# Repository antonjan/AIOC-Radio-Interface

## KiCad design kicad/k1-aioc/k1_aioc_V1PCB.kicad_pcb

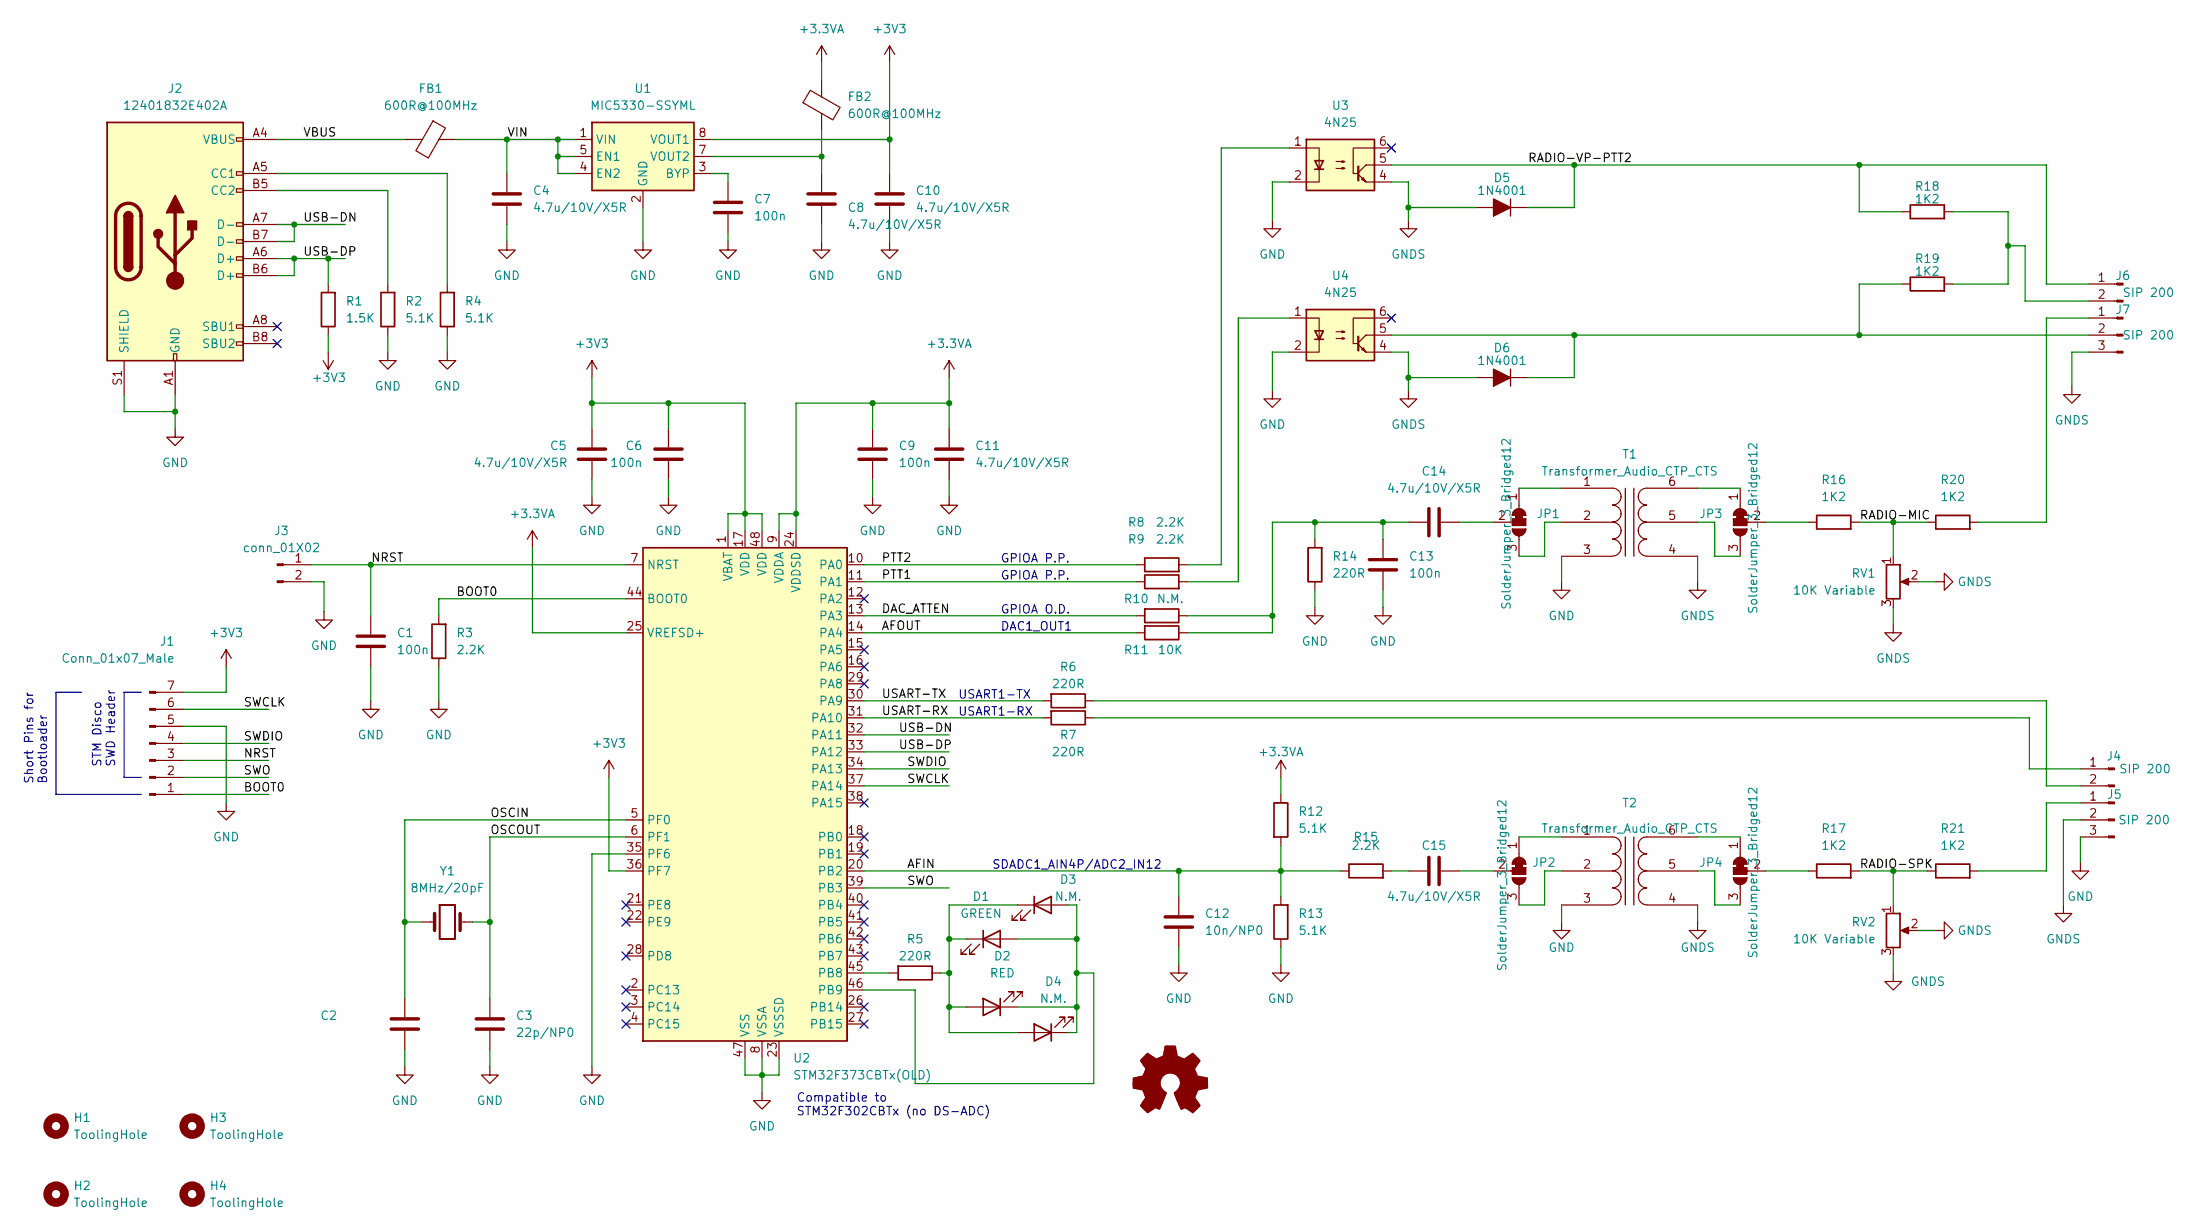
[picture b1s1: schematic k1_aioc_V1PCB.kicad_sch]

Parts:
C1, C6, C7, C9, C13: 100n; C_0805_2012Metric_Pad1.18x1.45mm_HandSolder; LCSC C14663
C2: LCSC C1653
C3: 22p/NP0; C_0805_2012Metric_Pad1.18x1.45mm_HandSolder; LCSC C1653
C4, C5, C8, C10, C11, C14, C15: 4.7u/10V/X5R; C_0805_2012Metric_Pad1.18x1.45mm_HandSolder; LCSC C19666
C12: 10n/NP0; C_0805_2012Metric_Pad1.18x1.45mm_HandSolder; LCSC C57112
D1: GREEN; LED_0805_2012Metric_Pad1.15x1.40mm_HandSolder; LCSC C72043
D2: RED; LED_0805_2012Metric_Pad1.15x1.40mm_HandSolder; LCSC C2286
D3, D4: N.M.; LED_0805_2012Metric_Pad1.15x1.40mm_HandSolder
D5, D6: 1N4001; D_0805_2012Metric_Pad1.15x1.40mm_HandSolder
FB1, FB2: 600R@100MHz; L_0805_2012Metric_Pad1.15x1.40mm_HandSolder; LCSC C1002
H1, H2, H3, H4: ToolingHole; MountingHole_3.2mm_M3_DIN965_Pad_TopBottom
J1: Conn_01x07_Male; PinHeader_1x07_P1.27mm_Vertical
J2: 12401832E402A; USB_C_Receptacle_Amphenol_12401832E40-2A; LCSC C464604
J3: conn_01X02; PinHeader_1x02_P2.54mm_Vertical
J4, J6: SIP 200; TerminalBlock_bornier-2_P5.08mm
J5, J7: SIP 200; TerminalBlock_bornier-3_P5.08mm
JP1, JP2, JP3, JP4: SolderJumper_3_Bridged12; SolderJumper-3_P1.3mm_Bridged12_RoundedPad1.0x1.5mm_NumberL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
R1: 1.5K; R_0805_2012Metric_Pad1.20x1.40mm_HandSolder; LCSC C22843
R2, R4, R12, R13: 5.1K; R_0805_2012Metric_Pad1.20x1.40mm_HandSolder; LCSC C23186
R3, R8, R9, R15: 2.2K; R_0805_2012Metric_Pad1.20x1.40mm_HandSolder; LCSC C4190
R5, R6, R7, R14: 220R; R_0805_2012Metric_Pad1.20x1.40mm_HandSolder; LCSC C22962
R10: N.M.; R_0805_2012Metric_Pad1.20x1.40mm_HandSolder
R11: 10K; R_0805_2012Metric_Pad1.20x1.40mm_HandSolder; LCSC C25804
R16, R17, R18, R19, R20, R21: 1K2; R_0805_2012Metric_Pad1.20x1.40mm_HandSolder
RV1, RV2: 10K Variable; Potentiometer_Bourns_3314G_Vertical
T1, T2: Transformer_Audio_CTP_CTS; Transformer_Bourns_SM-LP-5001
U1: MIC5330-SSYML; Micrel_MLF-8-1EP_2x2mm_P0.5mm_EP0.6x1.2mm; LCSC C144168
U2: STM32F373CBTx(OLD); LQFP-48_7x7mm_P0.5mm; LCSC C94046
U3, U4: 4N25; DIP-6_W8.89mm_SMDSocket_LongPads
Y1: 8MHz/20pF; Crystal_8MHz_SMD_11.40mm; LCSC C115962

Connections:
+3.3VA: C9.1, C11.1, FB2.1, R12.1, U2.9 (VDDA), U2.24 (VDDSD), U2.25 (VREFSD+)
+3V3: C5.1, C6.1, C10.1, J1.7, R1.1, U1.8 (VOUT1), U2.1 (VBAT), U2.17 (VDD), U2.36 (PF7), U2.48 (VDD)
/AFIN: C12.1, R12.2, R13.2, R15.1, U2.20 (PB2)
/AFOUT: R11.2, U2.14 (PA4)
/BOOT0: J1.1, R3.2, U2.44 (BOOT0)
/DAC_ATTEN: R10.2, U2.13 (PA3)
/NRST: C1.1, J1.3, J3.1, U2.7 (NRST)
/OSCIN: C2.1, U2.5 (PF0), Y1.1
/OSCOUT: C3.1, U2.6 (PF1), Y1.2
/PTT1: R9.1, U2.11 (PA1)
/PTT2: R8.1, U2.10 (PA0)
/RADIO-MIC: R16.2, R20.1, RV1.1
/RADIO-SPK: R17.2, R21.1, RV2.1
/RADIO-VP-PTT2: D5.1 (K), J6.1, R18.1, U3.5
/SWCLK: J1.6, U2.37 (PA14)
/SWDIO: J1.4, U2.34 (PA13)
/SWO: J1.2, U2.39 (PB3)
/USART-RX: R7.2, U2.31 (PA10)
/USART-TX: R6.2, U2.30 (PA9)
/USB-DN: J2.A7 (D-), J2.B7 (D-), U2.32 (PA11)
/USB-DP: J2.A6 (D+), J2.B6 (D+), R1.2, U2.33 (PA12)
/VBUS: FB1.2, J2.A4 (VBUS), J2.A9 (VBUS), J2.B4 (VBUS), J2.B9 (VBUS)
/VIN: C4.1, FB1.1, U1.1 (VIN), U1.4 (EN2), U1.5 (EN1)
GND: C1.2, C2.2, C3.2, C4.2, C5.2, C6.2, C7.2, C8.2, C9.2, C10.2, C11.2, C12.2, C13.2, J1.5, J2.A1 (GND), J2.A12 (GND), J2.B1 (GND), J2.B12 (GND), J2.S1 (SHIELD), J3.2, J5.3, R2.1, R3.1, R4.1, R13.1, R14.1, T1.3 (PR2), T2.3 (PR2), U1.2 (GND), U1.9 (GND), U2.8 (VSSA), U2.23 (VSSSD), U2.35 (PF6), U2.47 (VSS), U3.2, U4.2
GNDS: D5.2 (A), D6.2 (A), J5.2, J7.3, RV1.2, RV1.3, RV2.2, RV2.3, T1.4 (S1), T2.4 (S1), U3.4, U4.4
unnamed: C7.1, U1.3 (BYP)
unnamed: C8.1, FB2.2, U1.7 (VOUT2)
unnamed: C13.1, C14.1, R10.1, R11.1, R14.2
unnamed: C14.2, JP1.2 (C)
unnamed: C15.1, R15.2
unnamed: C15.2, JP2.2 (C)
unnamed: D1.1 (K), D2.2 (A), D3.1 (K), D4.2 (A), R5.1
unnamed: D1.2 (A), D2.1 (K), D3.2 (A), D4.1 (K), U2.46 (PB9)
unnamed: D6.1 (K), J7.2, R19.1, U4.5
unnamed: J2.A5 (CC1), R4.2
unnamed: J2.B5 (CC2), R2.2
unnamed: J4.1, R7.1
unnamed: J4.2, R6.1
unnamed: J5.1, R21.2
unnamed: J6.2, R18.2, R19.2
unnamed: J7.1, R20.2
unnamed: JP1.1 (A), T1.1 (PR1)
unnamed: JP1.3 (B), T1.2 (PM)
unnamed: JP2.1 (A), T2.1 (PR1)
unnamed: JP2.3 (B), T2.2 (PM)
unnamed: JP3.1 (A), T1.6 (S2)
unnamed: JP3.2 (C), R16.1
unnamed: JP3.3 (B), T1.5 (SE)
unnamed: JP4.1 (A), T2.6 (S2)
unnamed: JP4.2 (C), R17.1
unnamed: JP4.3 (B), T2.5 (SE)
unnamed: R5.2, U2.45 (PB8)
unnamed: R8.2, U3.1
unnamed: R9.2, U4.1

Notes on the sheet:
STM Disco SWD Header
Short Pins for Bootloader
SDADC1_AIN4P/ADC2_IN12
USART1-TX
GPIOA P.P.
DAC1_OUT1
GPIOA O.D.
Compatible to STM32F302CBTx (no DS-ADC)
USART1-RX

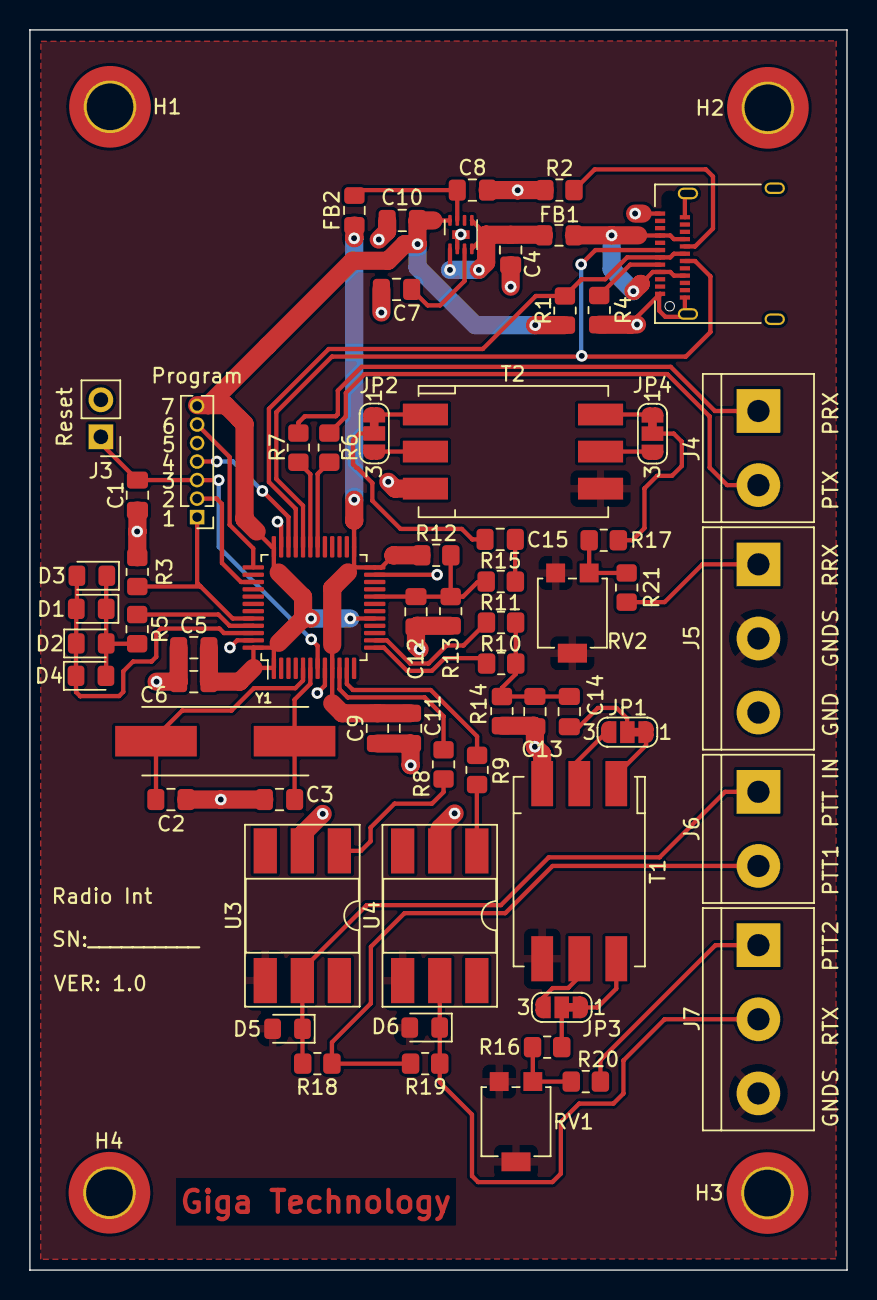
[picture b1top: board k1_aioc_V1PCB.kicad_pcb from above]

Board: 2 copper layers, 56.0 x 85.0 mm, 68 parts (0 on the bottom side), 54 nets.

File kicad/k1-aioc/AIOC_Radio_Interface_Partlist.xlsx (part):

Column1 | Column2 | Reference(s) | Value | LibPart | Footprint | Datasheet | LCSC | DigiKey Part NR | Mouser Part NR
Source: | C:\Users\jacqu\OneDrive\Desktop\WORK\AIOC_Radio_Interface\AIOC-Radio-Interface\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
Date: | 2023/07/28 10:16:02
Tool: | Eeschema (6.0.4)
Generator: | C:\Program Files\KiCad\6.0\bin\scripting\plugins/bom_csv_grouped_by_value.py
Component Count: | 64
Individual Components:
Item | Qty | Reference(s) | Value | LibPart | Footprint | Datasheet | LCSC | DigiKey Part NR | Mouser Part NR
 |  | C1 | 100n | Device:C | Capacitor_SMD:C_0805_2012Metric_Pad1.18x1.45mm_HandSolder | https://www.mouser.co.za/datasheet/2/585/MLCC_Automotive-183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 | C14663 |  | 187-CL21B104KBFWPJE
 |  | C2 | 22p/NP0 | Device:C | Capacitor_SMD:C_0805_2012Metric_Pad1.18x1.45mm_HandSolder | https://www.mouser.co.za/datasheet/2/210/WTC_MLCC_General_Pu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 | C1653 |  | 791-0805N220J160CT
 |  | C3 | 22p/NP0 | Device:C | Capacitor_SMD:C_0805_2012Metric_Pad1.18x1.45mm_HandSolder | https://www.mouser.co.za/datasheet/2/210/WTC_MLCC_General_Pu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 | C1653 |  | 791-0805N220J160CT
 |  | C4 | 4.7u/10V/X5R | Device:C | Capacitor_SMD:C_0805_2012Metric_Pad1.18x1.45mm_HandSolder | https://www.mouser.co.za/datasheet/2/585/MLCC-1837944.pdf | C19666 |  | 187-CL21A475KPFNNNG
 |  | C5 | 4.7u/10V/X5R | Device:C | Capacitor_SMD:C_0805_2012Metric_Pad1.18x1.45mm_HandSolder | https://www.mouser.co.za/datasheet/2/585/MLCC-1837944.pdf | C19666 |  | 187-CL21A475KPFNNNG
 |  | C6 | 100n | Device:C | Capacitor_SMD:C_0805_2012Metric_Pad1.18x1.45mm_HandSolder | https://www.mouser.co.za/datasheet/2/585/MLCC_Automotive-183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 | C14663 |  | 187-CL21B104KBFWPJE
 |  | C7 | 100n | Device:C | Capacitor_SMD:C_0805_2012Metric_Pad1.18x1.45mm_HandSolder | https://www.mouser.co.za/datasheet/2/585/MLCC_Automotive-183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 | C14663 |  | 187-CL21B104KBFWPJE
 |  | C8 | 4.7u/10V/X5R | Device:C | Capacitor_SMD:C_0805_2012Metric_Pad1.18x1.45mm_HandSolder | https://www.mouser.co.za/datasheet/2/585/MLCC-1837944.pdf | C19666 |  | 187-CL21A475KPFNNNG
 |  | C9 | 100n | Device:C | Capacitor_SMD:C_0805_2012Metric_Pad1.18x1.45mm_HandSolder | https://www.mouser.co.za/datasheet/2/585/MLCC_Automotive-183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 | C14663 |  | 187-CL21B104KBFWPJE
 |  | C10 | 4.7u/10V/X5R | Device:C | Capacitor_SMD:C_0805_2012Metric_Pad1.18x1.45mm_HandSolder | https://www.mouser.co.za/datasheet/2/585/MLCC-1837944.pdf | C19666 |  | 187-CL21A475KPFNNNG
 |  | C11 | 4.7u/10V/X5R | Device:C | Capacitor_SMD:C_0805_2012Metric_Pad1.18x1.45mm_HandSolder | https://www.mouser.co.za/datasheet/2/585/MLCC-1837944.pdf | C19666 |  | 187-CL21A475KPFNNNG
 |  | C12 | 10n/NP0 | Device:C | Capacitor_SMD:C_0805_2012Metric_Pad1.18x1.45mm_HandSolder | https://www.mouser.co.za/datasheet/2/210/WTC_MLCC_General_Pu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 | C57112 |  | 791-0805N100G250CT
 |  | C13 | 100n | Device:C | Capacitor_SMD:C_0805_2012Metric_Pad1.18x1.45mm_HandSolder | https://www.mouser.co.za/datasheet/2/585/MLCC_Automotive-183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 | C14663 |  | 187-CL21B104KBFWPJE
 |  | C14 | 4.7u/10V/X5R | Device:C | Capacitor_SMD:C_0805_2012Metric_Pad1.18x1.45mm_HandSolder | https://www.mouser.co.za/datasheet/2/585/MLCC-1837944.pdf | C19666 |  | 187-CL21A475KPFNNNG
 |  | C15 | 4.7u/10V/X5R | Device:C | Capacitor_SMD:C_0805_2012Metric_Pad1.18x1.45mm_HandSolder | https://www.mouser.co.za/datasheet/2/585/MLCC-1837944.pdf | C19666 |  | 187-CL21A475KPFNNNG
 |  | D1 | GREEN | Device:LED | LED_SMD:LED_0805_2012Metric_Pad1.15x1.40mm_HandSolder | https://www.mouser.co.za/datasheet/2/244/LUMX_S_A0011391738_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 | C72043 |  | 696-SML-LXT0805GW
 |  | D2 | RED | Device:LED | LED_SMD:LED_0805_2012Metric_Pad1.15x1.40mm_HandSolder | https://www.mouser.co.za/datasheet/2/216/ap2012serieskb-1173158.pdf | C2286 |  | 604-AP2012ID
 |  | D3 | N.M. | Device:LED | LED_SMD:LED_0805_2012Metric_Pad1.15x1.40mm_HandSolder | ~
 |  | D4 | N.M. | Device:LED | LED_SMD:LED_0805_2012Metric_Pad1.15x1.40mm_HandSolder | ~
 |  | D5 | 1N4001 | Audio_transformer:D_ALT | Diode_SMD:D_0805_2012Metric_Pad1.15x1.40mm_HandSolder
 |  | D6 | 1N4001 | Audio_transformer:D_ALT | Diode_SMD:D_0805_2012Metric_Pad1.15x1.40mm_HandSolder
 |  | FB1 | 600R@100MHz | Device:FerriteBead | Inductor_SMD:L_0805_2012Metric_Pad1.15x1.40mm_HandSolder | ~ | C1002
 |  | FB2 | 600R@100MHz | Device:FerriteBead | Inductor_SMD:L_0805_2012Metric_Pad1.15x1.40mm_HandSolder | ~ | C1002
 |  | J1 | Conn_01x07_Male | Connector:Conn_01x07_Male | Connector_PinHeader_1.27mm:PinHeader_1x07_P1.27mm_Vertical | ~
 |  | J2 | 12401832E402A | Connector:USB_C_Receptacle_USB2.0 | AIOC:USB_C_Receptacle_Amphenol_12401832E40-2A | https://www.usb.org/sites/default/files/documents/usb_type-c.zip | C464604
 |  | J3 | conn_01X02 | Connector:Conn_01x02_Male | Connector_PinHeader_2.54mm:PinHeader_1x02_P2.54mm_Vertical | ~
 |  | J4 | SIP 200 | Connector:Conn_01x02_Male | TerminalBlock:TerminalBlock_bornier-2_P5.08mm | ~
 |  | J5 | SIP 200 | Connector:Conn_01x03_Male | TerminalBlock:TerminalBlock_bornier-3_P5.08mm | ~
 |  | J6 | SIP 200 | Connector:Conn_01x02_Male | TerminalBlock:TerminalBlock_bornier-2_P5.08mm | ~
 |  | J7 | SIP 200 | Connector:Conn_01x03_Male | TerminalBlock:TerminalBlock_bornier-3_P5.08mm | ~
 |  | JP1 | SolderJumper_3_Bridged12 | Jumper:SolderJumper_3_Bridged12 | Jumper:SolderJumper-3_P1.3mm_Bridged12_RoundedPad1.0x1.5mm_NumberLabels | ~
 |  | JP2 | SolderJumper_3_Bridged12 | Jumper:SolderJumper_3_Bridged12 | Jumper:SolderJumper-3_P1.3mm_Bridged12_RoundedPad1.0x1.5mm_NumberLabels | ~
 |  | JP3 | SolderJumper_3_Bridged12 | Jumper:SolderJumper_3_Bridged12 | Jumper:SolderJumper-3_P1.3mm_Bridged12_RoundedPad1.0x1.5mm_NumberLabels | ~
 |  | JP4 | SolderJumper_3_Bridged12 | Jumper:SolderJumper_3_Bridged12 | Jumper:SolderJumper-3_P1.3mm_Bridged12_RoundedPad1.0x1.5mm_NumberLabels | ~
 |  | R1 | 1.5K | Device:R | Resistor_SMD:R_0805_2012Metric_Pad1.20x1.40mm_HandSolder | ~ | C22843
 |  | R2 | 5.1K | Device:R | Resistor_SMD:R_0805_2012Metric_Pad1.20x1.40mm_HandSolder | ~ | C23186
 |  | R3 | 2.2K | Device:R | Resistor_SMD:R_0805_2012Metric_Pad1.20x1.40mm_HandSolder | ~ | C4190
 |  | R4 | 5.1K | Device:R | Resistor_SMD:R_0805_2012Metric_Pad1.20x1.40mm_HandSolder | ~ | C23186
 |  | R5 | 220R | Device:R | Resistor_SMD:R_0805_2012Metric_Pad1.20x1.40mm_HandSolder | ~ | C22962
 |  | R6 | 220R | Device:R | Resistor_SMD:R_0805_2012Metric_Pad1.20x1.40mm_HandSolder | ~ | C22962
 |  | R7 | 220R | Device:R | Resistor_SMD:R_0805_2012Metric_Pad1.20x1.40mm_HandSolder | ~ | C22962
 |  | R8 | 2.2K | Device:R | Resistor_SMD:R_0805_2012Metric_Pad1.20x1.40mm_HandSolder | ~ | C4190
 |  | R9 | 2.2K | Device:R | Resistor_SMD:R_0805_2012Metric_Pad1.20x1.40mm_HandSolder | ~ | C4190
 |  | R10 | N.M. | Device:R | Resistor_SMD:R_0805_2012Metric_Pad1.20x1.40mm_HandSolder | ~
 |  | R11 | 10K | Device:R | Resistor_SMD:R_0805_2012Metric_Pad1.20x1.40mm_HandSolder | ~ | C25804
 |  | R12 | 5.1K | Device:R | Resistor_SMD:R_0805_2012Metric_Pad1.20x1.40mm_HandSolder | ~ | C23186
 |  | R13 | 5.1K | Device:R | Resistor_SMD:R_0805_2012Metric_Pad1.20x1.40mm_HandSolder | ~ | C23186
 |  | R14 | 220R | Device:R | Resistor_SMD:R_0805_2012Metric_Pad1.20x1.40mm_HandSolder | ~ | C22962
 |  | R15 | 2.2K | Device:R | Resistor_SMD:R_0805_2012Metric_Pad1.20x1.40mm_HandSolder | ~ | C4190
 |  | R16 | 1K2 | Device:R | Resistor_SMD:R_0805_2012Metric_Pad1.20x1.40mm_HandSolder | ~
 |  | R17 | 1K2 | Device:R | Resistor_SMD:R_0805_2012Metric_Pad1.20x1.40mm_HandSolder | ~
 |  | R18 | 1K2 | Device:R | Resistor_SMD:R_0805_2012Metric_Pad1.20x1.40mm_HandSolder | ~
 |  | R19 | 1K2 | Device:R | Resistor_SMD:R_0805_2012Metric_Pad1.20x1.40mm_HandSolder | ~
 |  | R20 | 1K2 | Device:R | Resistor_SMD:R_0805_2012Metric_Pad1.20x1.40mm_HandSolder | ~
 |  | R21 | 1K2 | Device:R | Resistor_SMD:R_0805_2012Metric_Pad1.20x1.40mm_HandSolder | ~
 |  | RV1 | 10K Variable | Device:R_Potentiometer | Potentiometer_SMD:Potentiometer_Bourns_3314G_Vertical | ~
 |  | RV2 | 10K Variable | Device:R_Potentiometer | Potentiometer_SMD:Potentiometer_Bourns_3314G_Vertical | ~
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
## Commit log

2023-07-14 adding files for backup
2023-07-19 updating files and adding usb datasheet
2023-07-26 Updating Kicad files for review
2024-07-19 Updating PCB files
